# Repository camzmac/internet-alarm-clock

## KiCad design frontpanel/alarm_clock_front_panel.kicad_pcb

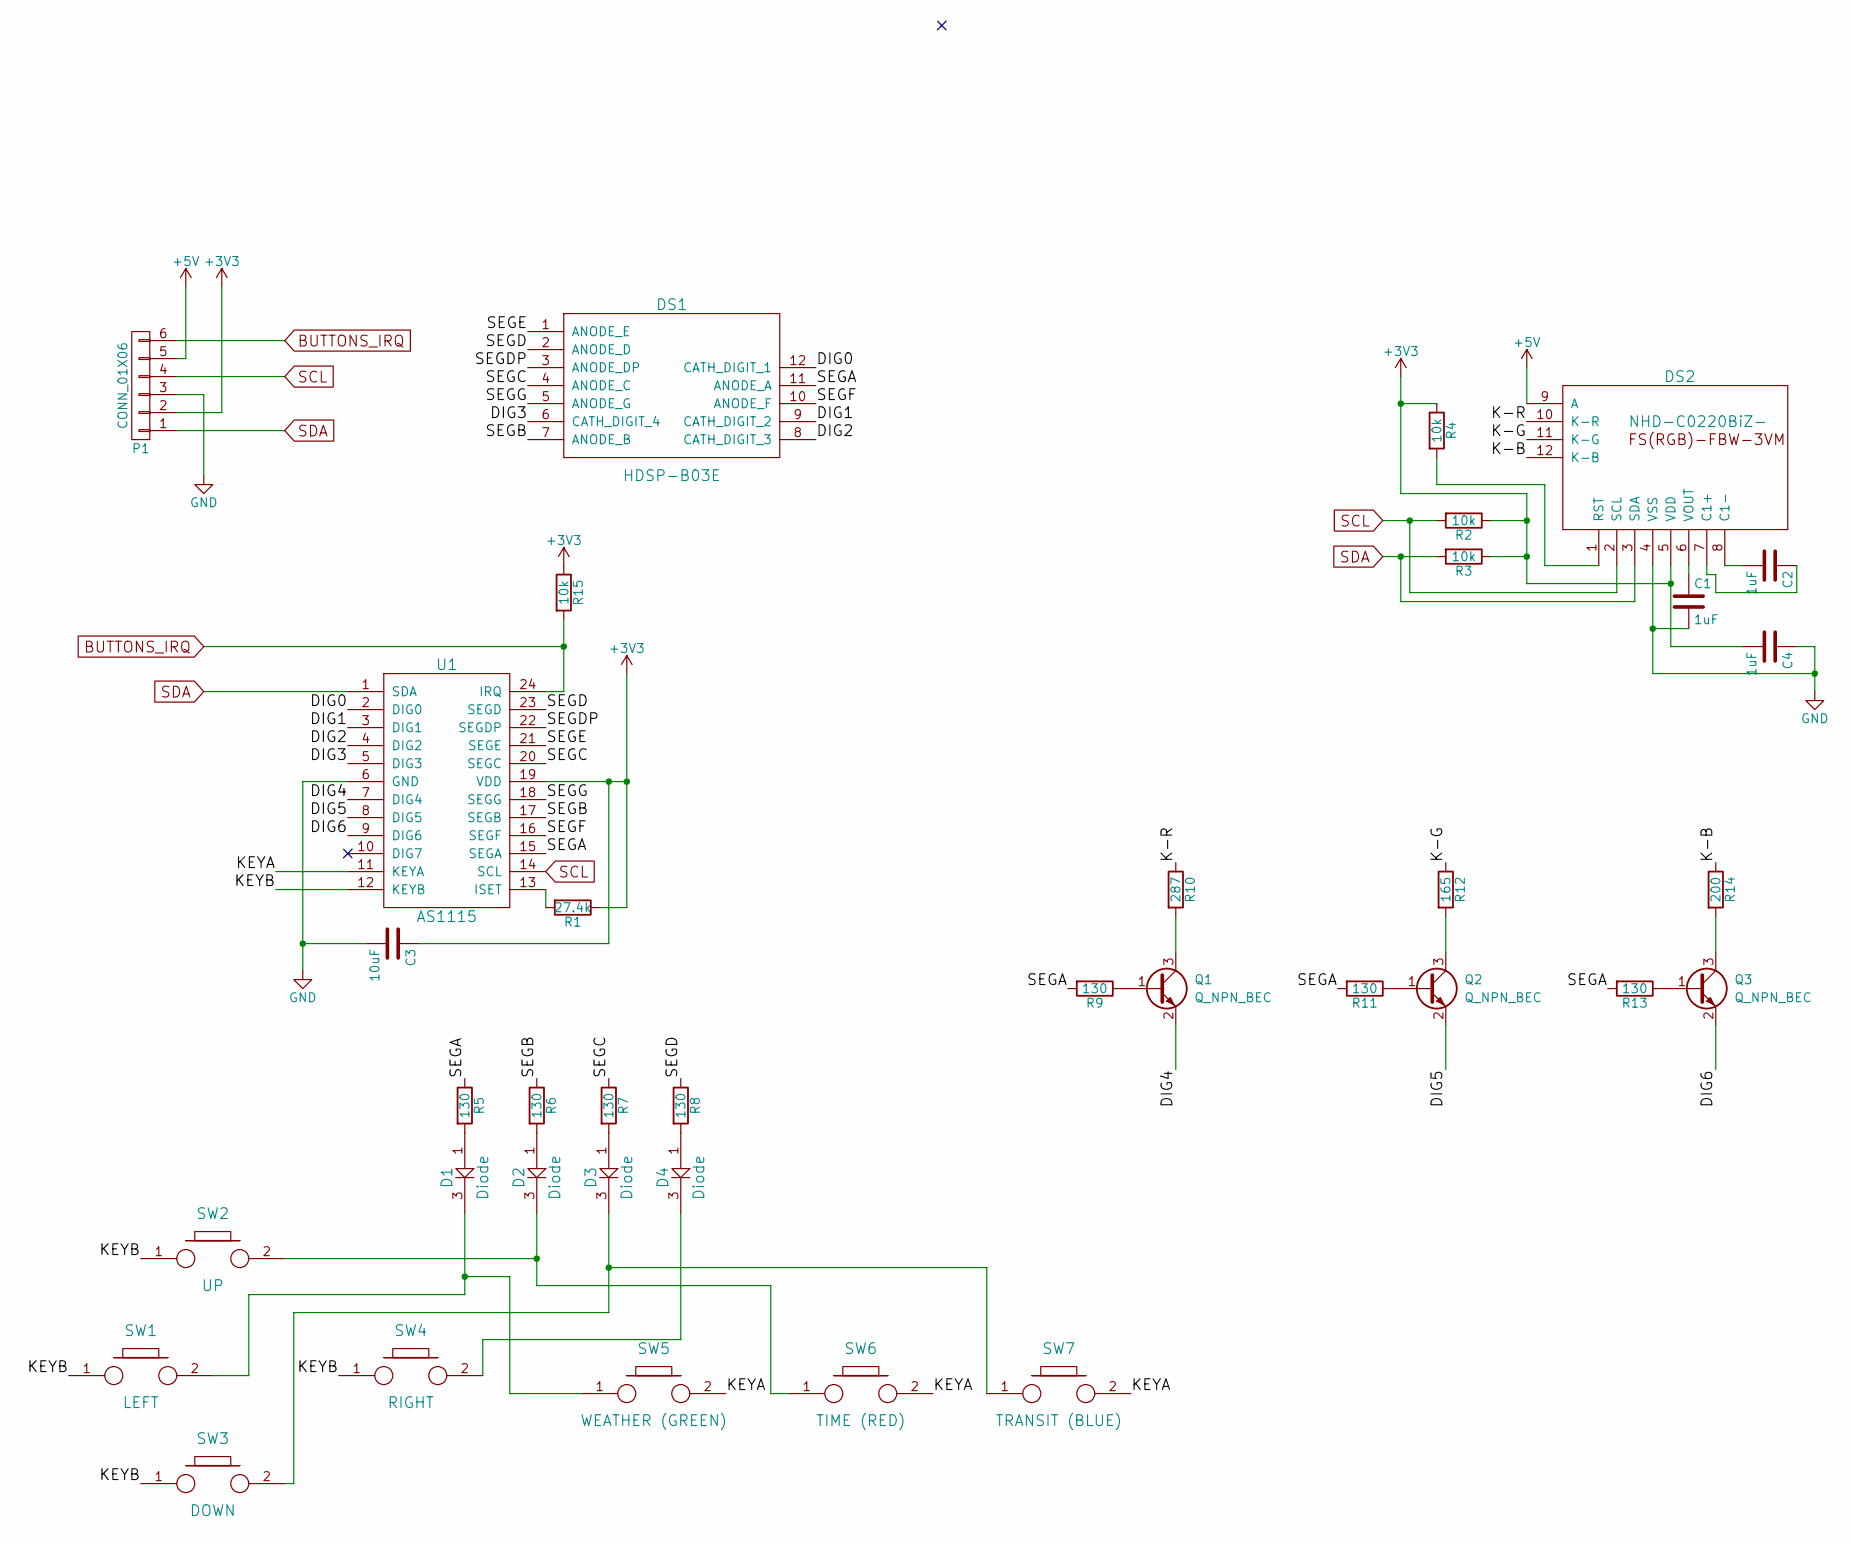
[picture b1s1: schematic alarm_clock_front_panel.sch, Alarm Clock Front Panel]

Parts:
C1, C2, C4: 1uF; C_1206_HandSoldering
C3: 10uF; C_1206_HandSoldering
D1, D2, D3, D4: Diode; SOT-23_Handsoldering
DS1: HDSP-B03E
DS2: NHD-C0220BiZ-; NHD-C0220BIZ-FS(RGB)-FBW-3VM
P1: CONN_01X06; IDC_Header_Straight_6pins
Q1, Q2, Q3: Q_NPN_BEC; SOT-23_Handsoldering
R1: 27.4k; R_1206_HandSoldering; Tolerance 1%
R2, R3, R4, R15: 10k; R_1206_HandSoldering
R5, R6, R7, R8, R9, R11, R13: 130; R_1206_HandSoldering
R10: 287; R_1206_HandSoldering
R12: 165; R_1206_HandSoldering
R14: 200; R_1206_HandSoldering
SW1: LEFT; TL1105SPF160Q
SW2: UP; TL1105SPF160Q
SW3: DOWN; TL1105SPF160Q
SW4: RIGHT; TL1105SPF160Q
SW5: WEATHER (GREEN); SW_Tactile_SPST_Angled
SW6: TIME (RED); SW_Tactile_SPST_Angled
SW7: TRANSIT (BLUE); SW_Tactile_SPST_Angled
U1: AS1115; SSOP-24_3.9x8.7mm_Pitch0.635mm

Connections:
+3V3: C3.1, C4.2, DS2.5 (VDD), P1.2, R1.1, R2.1, R3.1, R4.1, R15.1, U1.19 (VDD)
+5V: DS2.9 (A), P1.5
/DIG0: DS1.12 (CATH_DIGIT_1), U1.2 (DIG0)
/DIG1: DS1.9 (CATH_DIGIT_2), U1.3 (DIG1)
/DIG2: DS1.8 (CATH_DIGIT_3), U1.4 (DIG2)
/DIG3: DS1.6 (CATH_DIGIT_4), U1.5 (DIG3)
/DIG4: Q1.2 (E), U1.7 (DIG4)
/DIG5: Q2.2 (E), U1.8 (DIG5)
/DIG6: Q3.2 (E), U1.9 (DIG6)
/K-B: DS2.12 (K-B), R14.1
/K-G: DS2.11 (K-G), R12.1
/K-R: DS2.10 (K-R), R10.1
/KEYA: SW5.2, SW6.2, SW7.2, U1.11 (KEYA)
/KEYB: SW1.1, SW2.1, SW3.1, SW4.1, U1.12 (KEYB)
/SEGA: DS1.11 (ANODE_A), R5.1, R9.2, R11.2, R13.2, U1.15 (SEGA)
/SEGB: DS1.7 (ANODE_B), R6.1, U1.17 (SEGB)
/SEGC: DS1.4 (ANODE_C), R7.1, U1.20 (SEGC)
/SEGD: DS1.2 (ANODE_D), R8.1, U1.23 (SEGD)
/SEGDP: DS1.3 (ANODE_DP), U1.22 (SEGDP)
/SEGE: DS1.1 (ANODE_E), U1.21 (SEGE)
/SEGF: DS1.10 (ANODE_F), U1.16 (SEGF)
/SEGG: DS1.5 (ANODE_G), U1.18 (SEGG)
BUTTONS_IRQ: P1.6, R15.2, U1.24 (IRQ)
GND: C1.2, C3.2, C4.1, DS2.4 (VSS), P1.3, U1.6 (GND)
unnamed: C1.1, DS2.6 (VOUT)
unnamed: C2.1, DS2.7 (C1+)
unnamed: C2.2, DS2.8 (C1-)
unnamed: D1.1, R5.2
unnamed: D1.3, SW1.2, SW5.1
unnamed: D2.1, R6.2
unnamed: D2.3, SW2.2, SW6.1
unnamed: D3.1, R7.2
unnamed: D3.3, SW3.2, SW7.1
unnamed: D4.1, R8.2
unnamed: D4.3, SW4.2
unnamed: DS2.1 (RST), R4.2
unnamed: Q1.1 (B), R9.1
unnamed: Q1.3 (C), R10.2
unnamed: Q2.1 (B), R11.1
unnamed: Q2.3 (C), R12.2
unnamed: Q3.1 (B), R13.1
unnamed: Q3.3 (C), R14.2
unnamed: R1.2, U1.13 (ISET)
SCL: DS2.2 (SCL), P1.4, R2.2, U1.14 (SCL)
SDA: DS2.3 (SDA), P1.1, R3.2, U1.1 (SDA)

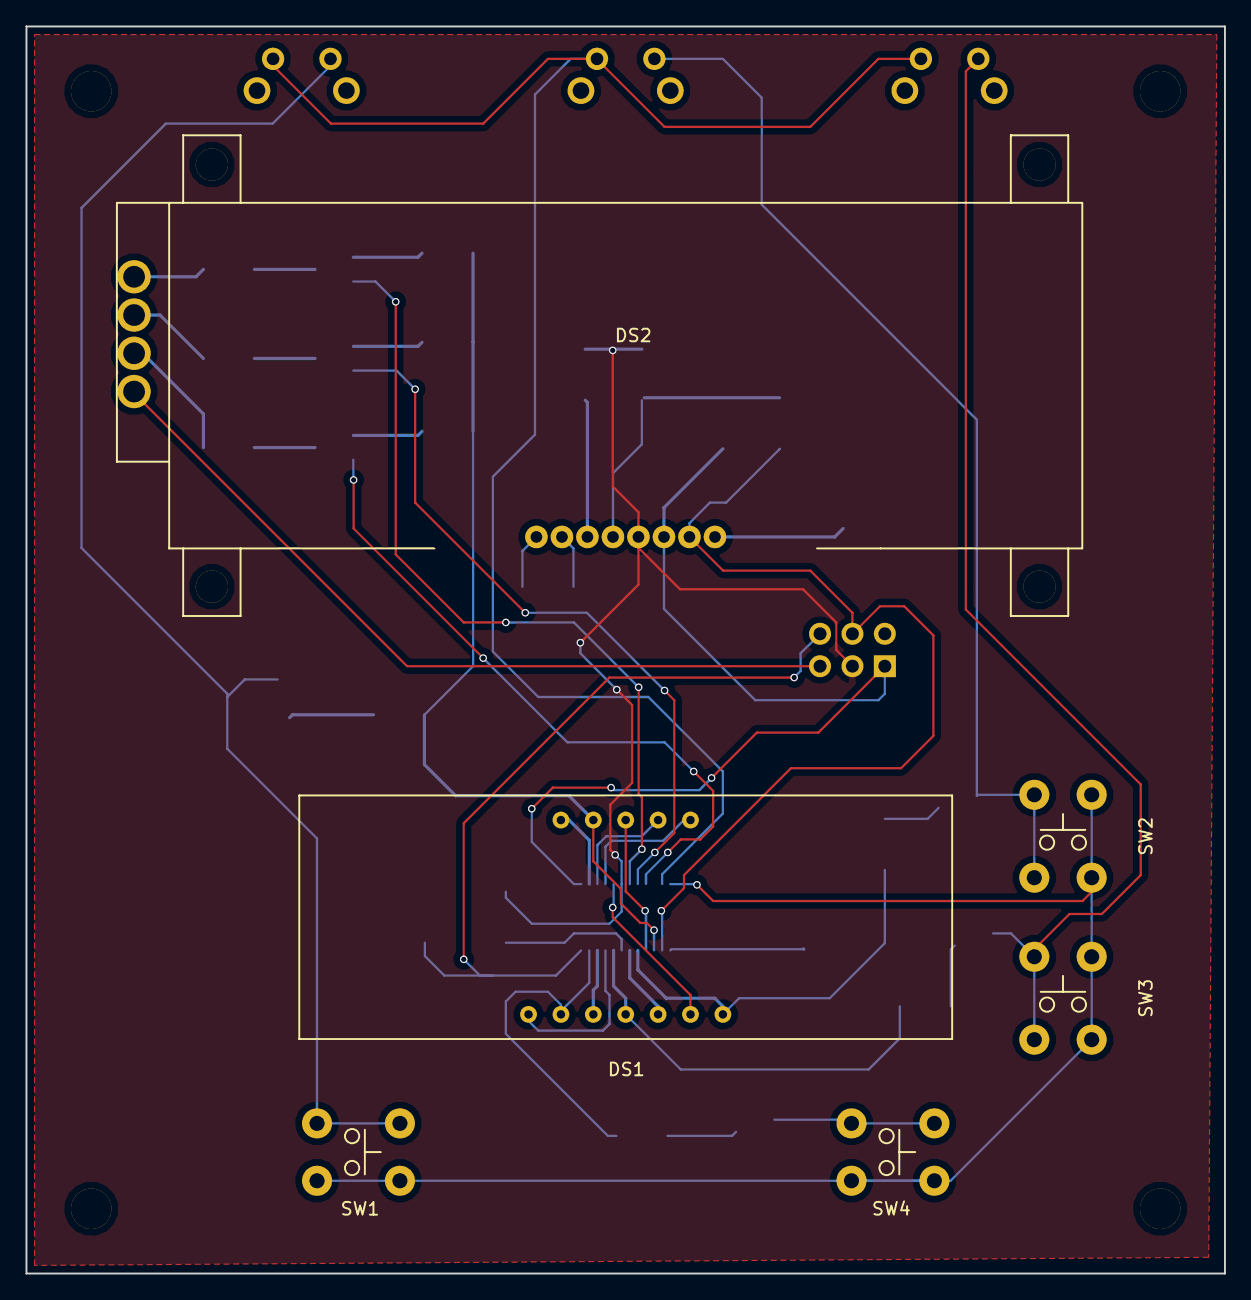
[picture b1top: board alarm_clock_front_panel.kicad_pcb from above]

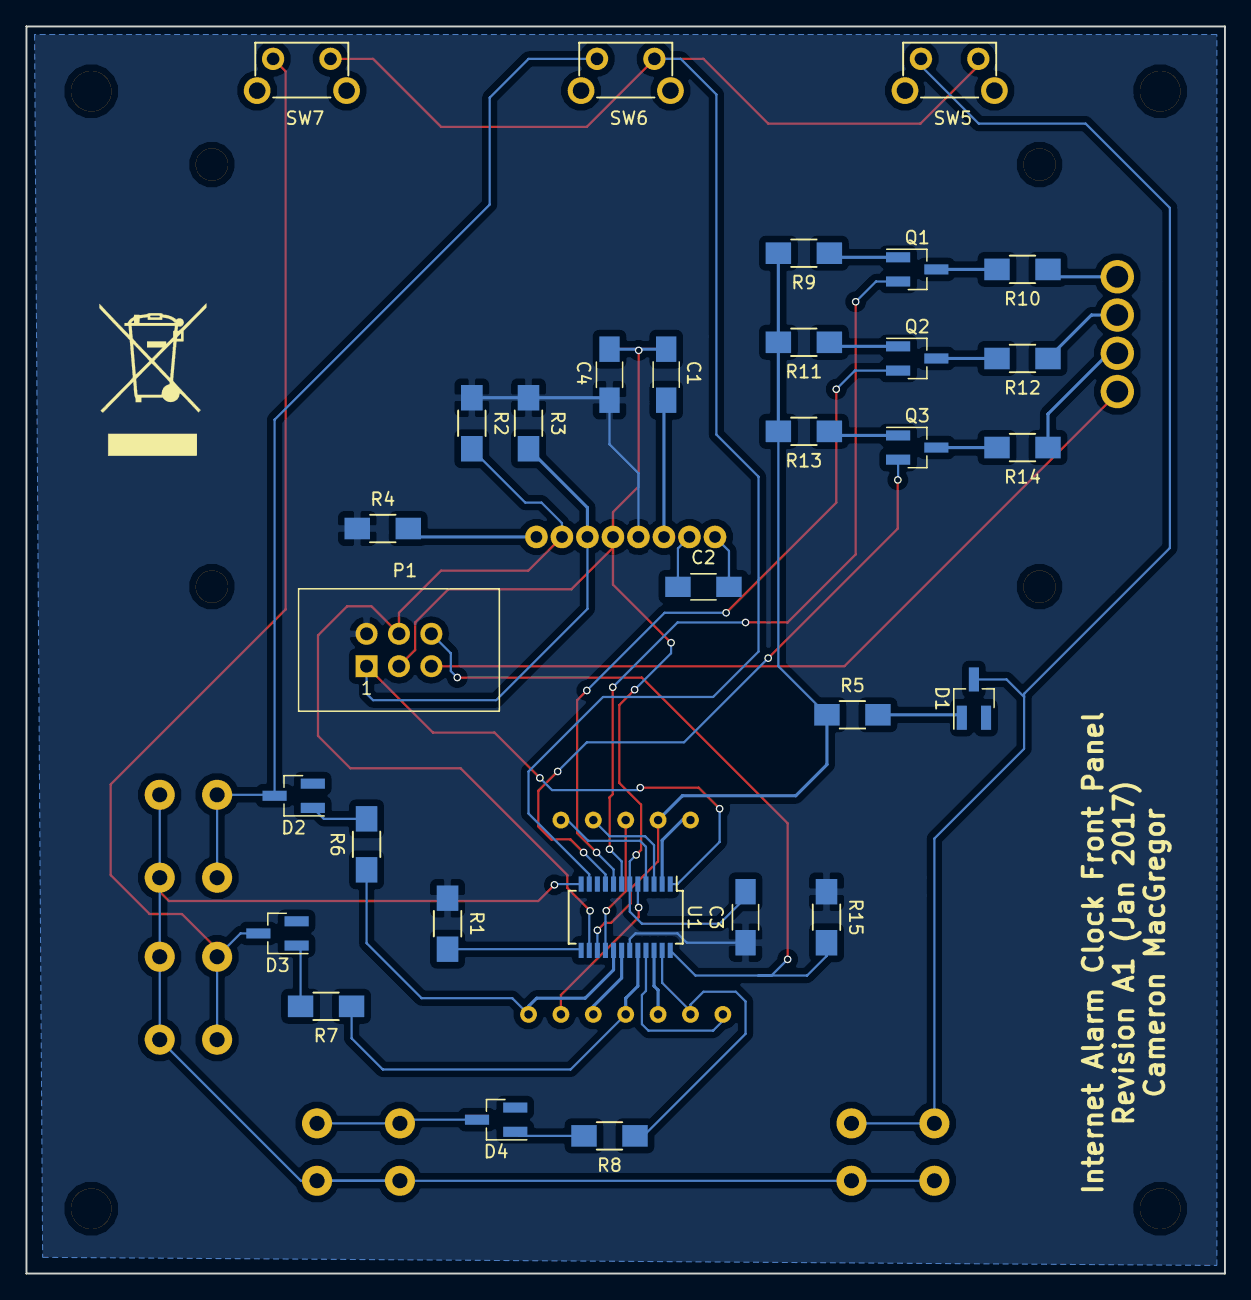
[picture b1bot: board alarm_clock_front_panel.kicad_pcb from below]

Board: 2 copper layers, 94.0 x 97.8 mm, 37 parts (31 on the bottom side), 45 nets.

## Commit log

2018-04-07 Started version control on Internet Alarm Clock project. Designed front panel user interface PCB with I2C bus and implemented basic alarm clock functionality in Lua with NodeMCU firmware on ESP8266.
2018-05-04 Added TI USCI I2C library, sample code for MSP430 (ESP8266 <-> MSP430 <-> front panel)
